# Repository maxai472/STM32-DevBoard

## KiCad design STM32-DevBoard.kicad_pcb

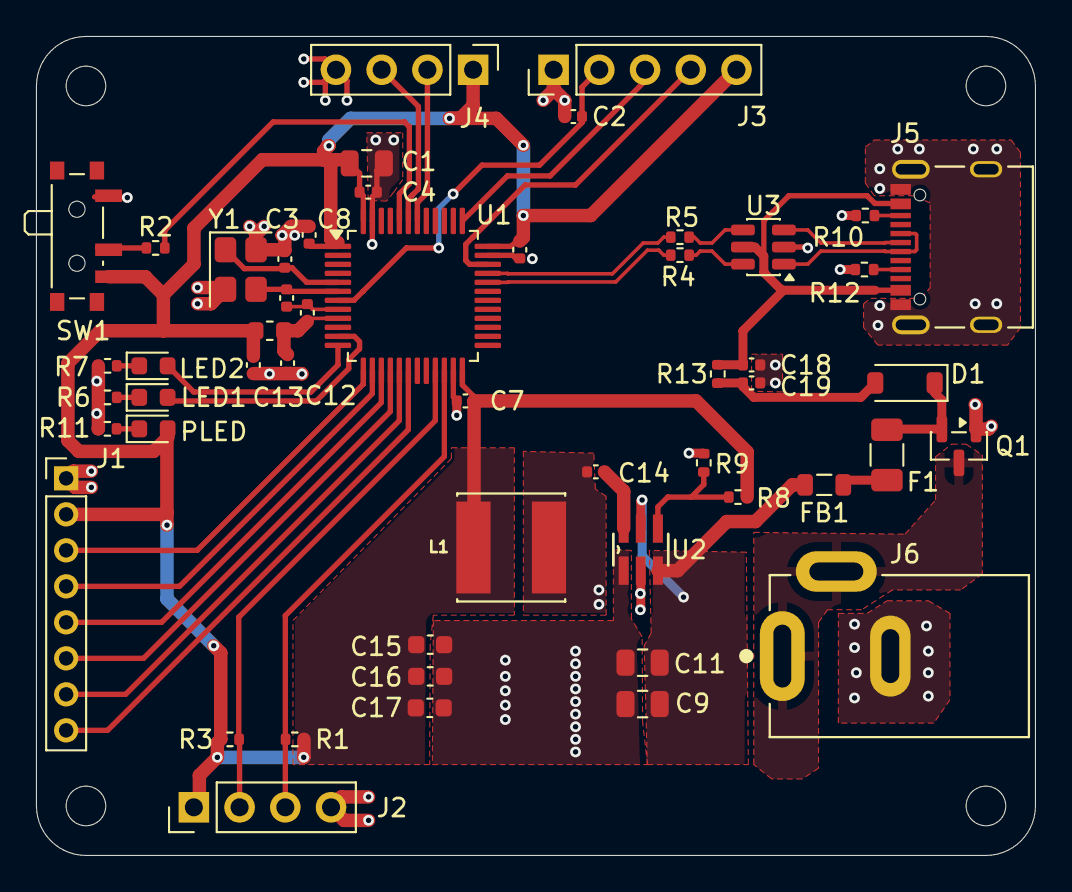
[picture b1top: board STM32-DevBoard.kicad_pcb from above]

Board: 2 copper layers, 55.5 x 45.5 mm, 56 parts (0 on the bottom side), 42 nets.

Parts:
C1, C9, C11: 10u; C_0805_2012Metric
C2, C4, C6, C7, C8, C10, C14: 100n; C_0402_1005Metric
C3, C5: 10p; C_0402_1005Metric
C12, C13: 1u; C_0402_1005Metric
C15, C16, C17: 22uF; C_0603_1608Metric
C18, C19: 470n; C_0402_1005Metric
D1: B5819W; D_SOD-123
F1: 250mA; Fuse_1206_3216Metric
FB1: 600 @ 600MHz; L_0805_2012Metric
FB2: 120R; L_0603_1608Metric
H1, H2, H3, H4: MountingHole; MountingHole_2.2mm_M2
J1: Conn_01x08_Pin; PinHeader_1x08_P2.00mm_Vertical
J2: I2C Bus 1; PinHeader_1x04_P2.54mm_Vertical
J3: Serial Debugger; PinHeader_1x05_P2.54mm_Vertical
J4: USART1; PinHeader_1x04_P2.54mm_Vertical
J5: 12402012E212A; AMPHENOL_12402012E212A
J6: PJ-002A; CUI_PJ-002A
L1: 2.2u; IND_VLS6045EX-2R2N
LED1: LED1; LED_0603_1608Metric
LED2: LED2; LED_0603_1608Metric
PLED: PLED; LED_0603_1608Metric
Q1: AO3401A; SOT-23
R1, R3: 4.7K; R_0402_1005Metric
R2, R9: 10k; R_0402_1005Metric
R4, R5: 22R; R_0402_1005Metric
R6, R7, R11: 1K; R_0402_1005Metric
R8: 33k2; R_0402_1005Metric
R10, R12: 5k1; R_0402_1005Metric
R13: R; R_0402_1005Metric
SW1: SW_SPDT; SW_SPDT_PCM12
U1: STM32F103C8T6; LQFP-48_7x7mm_P0.5mm
U2: TPS563209DDCR; DDC0006A
U3: USBLC6-2SC6; SOT-23-6
Y1: 16MHz; Crystal_SMD_3225-4Pin_3.2x2.5mm

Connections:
+3.3V: C1.1, C4.1, C6.1, C7.1, C8.1, C13.1, C15.1, C16.1, C17.1, FB2.2, J1.2, J2.1, J3.5, J4.1, L1.2, PLED.2 (A), R1.2, R3.2, R8.1, SW1.3 (C), U1.1 (VBAT), U1.24 (VDD), U1.36 (VDD), U1.48 (VDD)
+3.3VA: C10.1, C12.1, FB2.1, U1.9 (VDDA)
+12V: J6.1, J6.3, Q1.3 (D)
/+VIN_FILTERED: C9.1, C11.1, FB1.2, U2.3 (VIN), U2.5 (EN)
/+VIN_FUSED: F1.2, FB1.1
/+VIN_PROTECTED: D1.1 (K), F1.1, Q1.2 (S)
/BOOT0: R2.2, U1.44 (BOOT0)
/CC1_A: J5.A5 (CC1_A), R12.1
/CC1_B: J5.B5 (CC1_B), R10.1
/HSE_IN: C3.1, U1.5 (PD0), Y1.1
/HSE_OUT: C5.1, U1.6 (PD1), Y1.3
/LED1+: LED1.2 (A), U1.11 (PA1)
/LED1-: LED1.1 (K), R6.1
/LED2+: LED2.2 (A), U1.12 (PA2)
/LED2-: LED2.1 (K), R7.1
/PLED_OUT: PLED.1 (K), R11.2
/SW_BOOT0: R2.1, SW1.2 (B)
/SW_OUT: C14.1, L1.1, U2.2 (SW)
/USBC_D+: J5.A6 (D+_A), J5.B6 (D+_B), U3.1 (I/O1)
/USBC_D-: J5.A7 (D-_A), J5.B7 (D-_B), U3.3 (I/O2)
/VBST_OUT: C14.2, U2.6 (VBST)
/VFB_OUT: R8.2, R9.1, U2.4 (VFB)
GND: C1.2, C2.2, C3.2, C4.2, C5.2, C6.2, C7.2, C8.2, C9.2, C10.2, C11.2, C12.2, C13.2, C15.2, C16.2, C17.2, C18.2, C19.2, J1.1, J2.4, J3.1, J4.4, J5.A1_B12 (GND), J5.B1_A12 (GND__1), J5.SH1 (SHIELD), J5.SH2 (SHIELD__1), J5.SH3 (SHIELD__2), J5.SH4 (SHIELD__3), J6.2, Q1.1 (G), R6.2, R7.2, R9.2, R10.2, R11.1, R12.2, SW1.1 (A), U1.8 (VSSA), U1.23 (VSS), U1.35 (VSS), U1.47 (VSS), U2.1 (GND), U3.2 (GND), Y1.2, Y1.4
GPIO1: J1.3, U1.13 (PA3)
GPIO2: J1.4, U1.14 (PA4)
GPIO3: J1.5, U1.15 (PA5)
GPIO4: J1.6, U1.16 (PA6)
GPIO5: J1.7, U1.17 (PA7)
GPIO6: J1.8, U1.18 (PB0)
I2C1_SCL: J2.3, R1.1, U1.22 (PB11)
I2C1_SDA: J2.2, R3.1, U1.21 (PB10)
NRST: C2.1, J3.2, U1.7 (NRST)
unnamed: R4.1, U1.32 (PA11)
unnamed: R5.1, U1.33 (PA12)
SWCLK: J3.3, U1.37 (PA14)
SWDIO: J3.4, U1.34 (PA13)
USART1_RX: J4.3, U1.43 (PB7)
USART1_TX: J4.2, U1.42 (PB6)
USB_D+: R5.2, U3.4 (I/O2)
USB_D-: R4.2, U3.6 (I/O1)
VBUS: C18.1, J5.A4_B9 (VBUS), J5.B4_A9 (VBUS__1), R13.1, U3.5 (VBUS)
VBUSF: C19.1, D1.2 (A), R13.2

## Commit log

2026-02-17 Batman
2026-02-17 Schematic complete, preliminary pcb layout done
2026-02-18 Board constraints, layout, and initial traces done
2026-02-18 extra gpio
2026-02-20 part descs
2026-02-21 Added component information
2026-02-22 Added a bit more component information
2026-02-23 Added footprints and models, progressed PCB layout. TODO: rename nets
2026-03-09 Completed net names
2026-03-10 Routing progressed
2026-03-11 Routing Complete, need to finish off net labels
2026-03-11 Net labels partially complete, still more to go
2026-03-11 removed sync conflicts
